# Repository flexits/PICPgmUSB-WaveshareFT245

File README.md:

## PICPgm USB Programmer на основе модуля Waveshare FT245 USB FIFO Board (mini)

Схема и печатная плата программатора в KiCAD 6.  
Плата односторонняя для DIY.
Сделано на скорую руку для собственного использования, проверено с контроллером PIC12F1840, читает и пишет без проблем.  
ИМС `74LS14N` в моей реализации заменена на `К555ТЛ2` (просто потому что была в наличии); также вместо неё должны работать и более новая `КР1533ТЛ2`, и более старая `К155ТЛ2`.
### Erratum
- Разводка платы не оптимальна.  
- Также напутал с нумерацией контактов разъёма под Waveshare board, из-за чего в проекте пришлось поставить его на стороне дорожек. В реальности, конечно же, разъём припаивается как и положено, на лицевую сторону платы.  
- Пожалуй, имеет смысл входы неиспользуемых триггеров подтянуть к питанию, а не к земле.
- Пожалуй, привычнее будет плату отзеркалить, чтоб USB был слева, а панелька — справа, но это уже дело вкуса и конфигурации рабочего места. 
### Ссылки
Сайт проекта [PICPgm](http://picpgm.picprojects.net/index.html), там же утилита для работы с программатором.  
Драйвер FTDI D2xx [оф. сайт](https://ftdichip.com/drivers/d2xx-drivers/) (впрочем, на моём ПК с Win 10 установился автоматом).

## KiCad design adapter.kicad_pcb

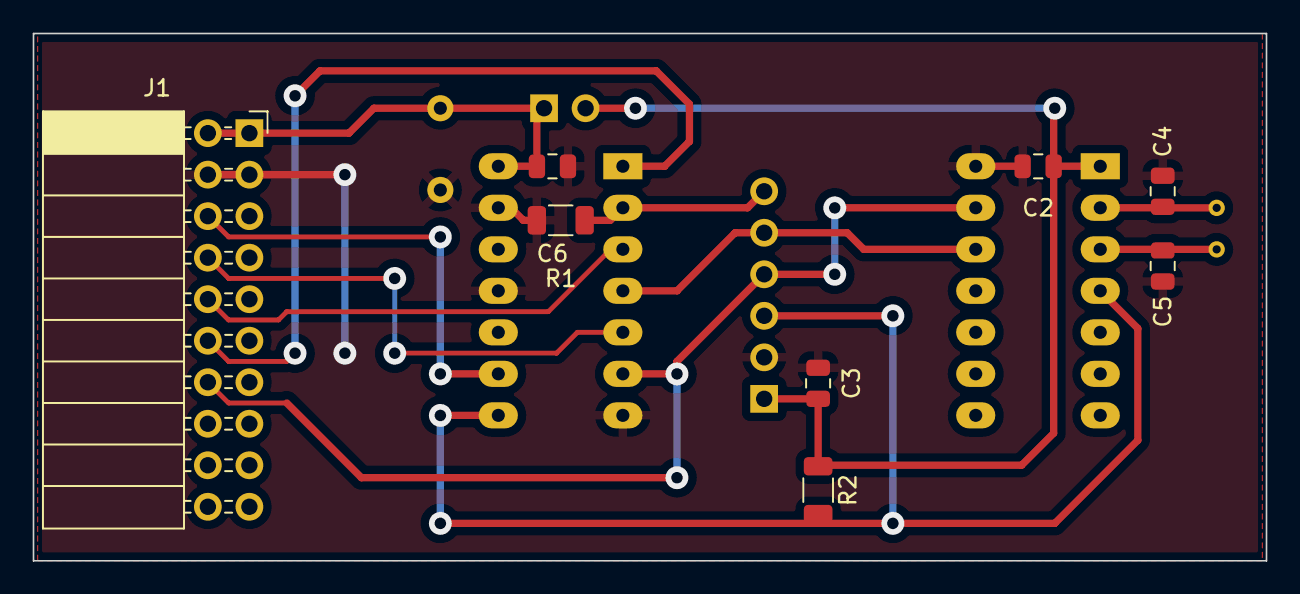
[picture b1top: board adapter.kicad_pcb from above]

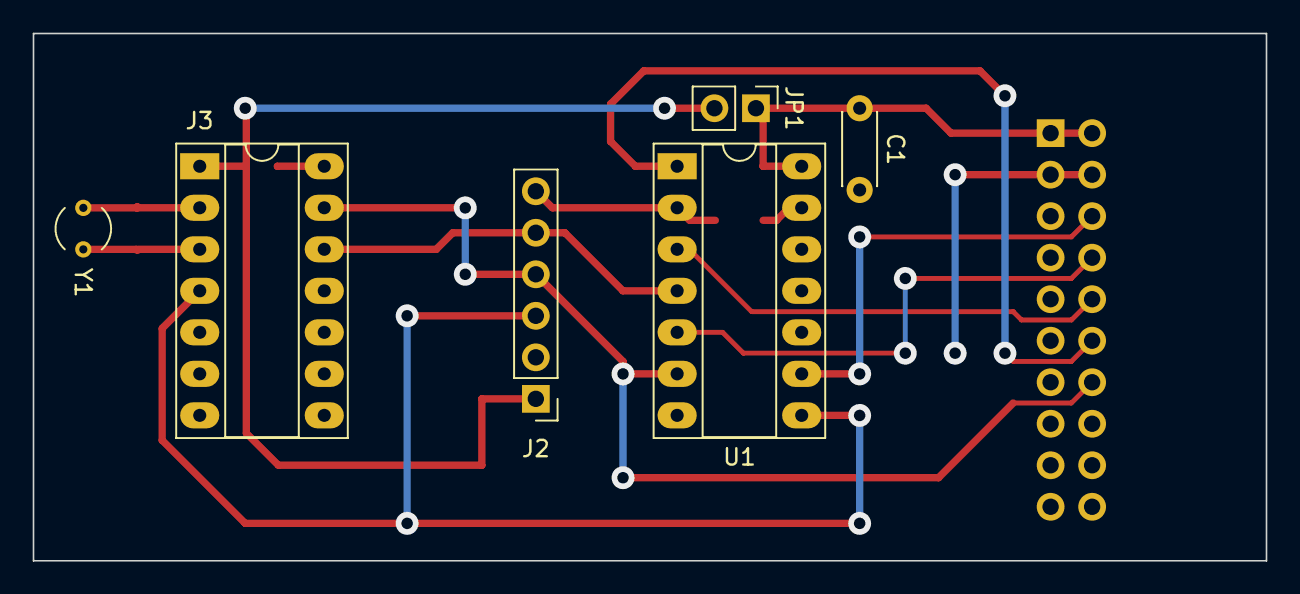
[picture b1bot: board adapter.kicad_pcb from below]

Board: 2 copper layers, 75.4 x 32.3 mm, 14 parts (6 on the bottom side), 13 nets.

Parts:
C1: 100n; C_Disc_D4.3mm_W1.9mm_P5.00mm
C2, C3, C6: 100n; C_0805_2012Metric
C4, C5: 22p; C_0805_2012Metric
J1: PBD-20R; PinSocket_2x10_P2.54mm_Horizontal
J2: PLS-6; PinHeader_1x06_P2.54mm_Vertical
J3: DS1044-14 panel; DIP-14_W7.62mm_Socket_LongPads
JP1: PLS-2; PinHeader_1x02_P2.54mm_Vertical
R1: 1k; R_1206_3216Metric
R2: 10k; R_1206_3216Metric
U1: 74LS14; DIP-14_W7.62mm_Socket_LongPads
Y1: Crystal; Crystal_AT310_D3.0mm_L10.0mm_Vertical

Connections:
+5V: C2.1, C3.1, J2.1, J3.1, JP1.2 (B), R2.1
GND: C1.2, C2.2, C3.2, C4.2, C5.2, C6.2, J1.3, J1.4, J2.2, J3.14, R1.1, U1.7 (GND), U1.11, U1.13
MCLR: J2.3, J3.4, R2.2, U1.8
unnamed: C4.1, J3.2, Y1.1
unnamed: C5.1, J3.3, Y1.2
unnamed: J1.8, U1.5
unnamed: J1.10, U1.3
unnamed: J1.12, U1.1
unnamed: J1.6, U1.9
PGC: J2.5, J3.12, U1.4
PGD: J1.14, J2.4, J3.13, U1.6
PGM: J2.6, R1.2, U1.2
VCC: C1.1, C6.1, J1.1, J1.2, JP1.1 (A), U1.14 (VCC)
